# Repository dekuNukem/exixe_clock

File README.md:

# exixe clock: nanosecond-precision GPS-disciplined Nixie tube clock

exixe clock is a GNSS-aided high precision Nixie tube clock.

With GPS fix acquired, displayed time would be within 60 **nanoseconds** of the atomic clocks onboard the satellites.

exixe clock makes use of the [exixe modules](https://github.com/dekuNukem/exixe), and works with both IN-14 and IN-12 tubes. It also comes with a wealth of sensors and interfaces on-board, allowing it to be hacked beyond just a timepiece.

## Video

Here's a short video of exixe clock in action with [exixe14 modules](https://github.com/dekuNukem/exixe) :

https://www.youtube.com/watch?v=r3d2alzgjKc

## Features

### Precision Timing

* 60ns with GPS fix
* less than 1 second per month drift without GPS fix
* Auto time acquisition
* Battery backup
* Customizable timezone

### Simple & modular construction

* Uses [exixe modules](https://github.com/dekuNukem/exixe)
* Works with both IN-12 and IN-14 tubes
* Single 5V supply from USB
* 350mA average consumption

### Versatile interfaces

* USB data transfer / firmware upload
* SD card slot
* Temperature sensor
* Light sensor
* UART extension header
* GNSS debug header
* 2 capacitive touch buttons
* 2 physical buttons
* GNSS fix indicator LED

## User guide

### Setting time

Install a CR1220 coin battery in the holder, connect a GPS antenna and place it under clear sky, time will be automatically set and saved when a GPS fix is obtained. You might have to wait 2 or 3 minutes, but it's usually much faster. Wait until the GPSFIX LED is on for the most accuracy.

### Setting timezone

Unplug the clock, hold down B button then power it back on. The middle two tube will display the UTC offset. Use A and B button to set the offset to your timezone. For negative offsets a dot on the left tube will illuminate.

### 12/24 hour display

Unplug the clock, hold down A button then power it back on. The middle two tube will display either 12 or 24. Use A button to change it.

### Temperature display

Press either A or B button during normal operation to switch the display to temperature in the rightmost two tubes, press it again to switch back.

## Extensions and hacks

There are some extra components that's worth mentioning if you want to further develop upon this project.

* A debug header is situated to the right of the USB port, you can use it for communication or extra GPIOs.

* The GPS header beside the antenna connector breaks out the TX, RX and timepulse of the GPS module, it's mainly for debugging purposes.

* There are 2 capacitive touchpad buttons, they are designed according to the ST reference doc and connected to TSC channels of the STM32, I haven't found a use for them yet though.

* A DFU button is available, hold it down while plugging the clock into a computer puts the STM32 into USB DFU mode, so you can upload firmware through USB without needing a programmer.

* You can use the empty pad of unused components for more GPIOs.

## Parts and tips

* MCU is STM32F072C8T6
* Light sensor is TEMT6000
* Temperature sensor is DS18B20
* GNSS receiver is ublox M8Q (M7Q also works)
* High voltage module is [this one](https://www.ebay.co.uk/itm/DC-5V-12V-to-170V-DC-High-Voltage-NIXIE-Power-Supply-Module-PSU-NIXIE-TUBE-ERA/322511957768?hash=item4b1735ef08:g:ftQAAOSwYTVZmjZb)
* There are two headers for the HV module, use the one that has the correct pinout
* Undefine `USE_EXIXE_14` at the beginning of [my_tasks.c](firmware/Src/my_tasks.c) to use IN-12 tubes.

## Building one yourself

BOM is [here](resources/clock_bom.xlsx)

Making one yourself is fairly straightforward, just order the parts and solder them together. Couple of things to keep in mind though:

There are a couple of optional components that is not used in the current firmware, so you can leave them out if you want, they are highlighted in yellow in the BOM

The temperature sensor DS18B20 has a lot of fakes on the internet, if it's too cheap it's almost certainly fake. Best way is just order through a reputable source like mouser or digikey, it is also optional if you don't want to use this feature.

DO NOT solder the GPS module by hand, it would result in terrible reliability where the GPS module would randomly stop working. Always use paste and reflow.

The PCB works with both exixe12 and exixe14 modules, the only different component is the SMA antenna connector. On clock using exixe14 modules, the right-angle SMA connector is used, while on clock using exixe12 module, a straight SMA connector is used instead. This allows the SMA receptacle point to the back of the clock in both cases.

Front and back plate are need with exixe12 clock to support the PCB inbetween, they are just regular laser cut clear acrylic plates, your local hackerspace should have a laser cutter. The plate files are in the `resources` folder.

You can go without plates with exixe14 clock, although I still recommend getting one for added rigidness. You only need one plate in this case.

To upload firmware to the microcontroller, [see this guide](https://github.com/dekuNukem/exixe/blob/master/making_some.md).

## Rants about conventional Nixie clocks

I was looking through existing Nixie clock projects before starting my own, and I'm rather unconvinced with some trends that many have in common:

* Using through hole components

While there's technically nothing wrong, I feel that in this day and age using PTH looks bulky and unprofessional.

* 12V supply

I want my clock to be powered by a single USB cable, using a 12V powerbrick is both cumbersome and complicates the design.

* Fixed and multiplexed tubes

This is my biggest gripe. With soldered down tubes, it's almost impossible to replace if one breaks, or to repurpose them for other projects. And as Nixie tubes have been out of productions for 30 years, they should be conserved as much as possible.

And as a result of fixed tubes, they are almost always multiplexed. This requires obscure driver chips, complex to route and program, and because only one tube is on at any given time, perceived brightness is 1/6 of what it could be. To compensate, the tubes are often overdriven beyond their max allowed current, reducing their life time. Total mess all around.

* Questionable timekeeping

Let's not forget Nixie clock is first and foremost a clock, and it's useless if it's not good at keeping time. However this aspect almost looks like an afterthought in a lot of the existing Nixie clocks. On many of those time have to be manually entered, and kept with $3 RTC modules from alibaba that drifts 20 seconds a month. I want my clock to be as accurate as possible.

## Things done differently

In the end, I decided to keep the design as modular and as simple as possible. As a result, I designed the exixe driver modules first, then the clock itself later. 

You can read more about the [exixe modules here](https://github.com/dekuNukem/exixe), but in short, they are tiny and inexpensive Nixie tube drivers with hardware PWM on all digits and RGB backlight. Each module controls one tube, and uses SPI for communication.

Now that each tube has its own driver, multiplexing is no longer needed, and routing is down to only 3 SPI lines, and each tube can be replaced and repurposed simply by unplugging the module.

Next up is timing, instead of manually setting time and using built-in RTC, I decided to use GPS-based timekeeping. There are atomic clocks onboard each GPS satellites, and the precise UTC time can be calculated as part of the position fix. This way time can be automatically set and kept within 60ns of GPS time with position fix. Each digit update is triggered by the timepulse signal from the GNSS receiver, synced to the precise transition of each UTC second. And if antenna is disconnected, drift seems to be than 1 second per month from the observation of the one I made myself. A coin battery keeps time even when the clock itself is turned off.

A bunch of extra features was thrown in during the design process as well. I added a temperature sensor so the tubes can optionally display hour:minute:temp instead of hour:minute:second, a blue LED lights up when GPS fix is acquired, 2 capacitive touchpad was added for buttonless controls, a light sensor was added for automatic brightness adjustment, SD card slot was added for data logging, and UART header was added for debugging and expansion.

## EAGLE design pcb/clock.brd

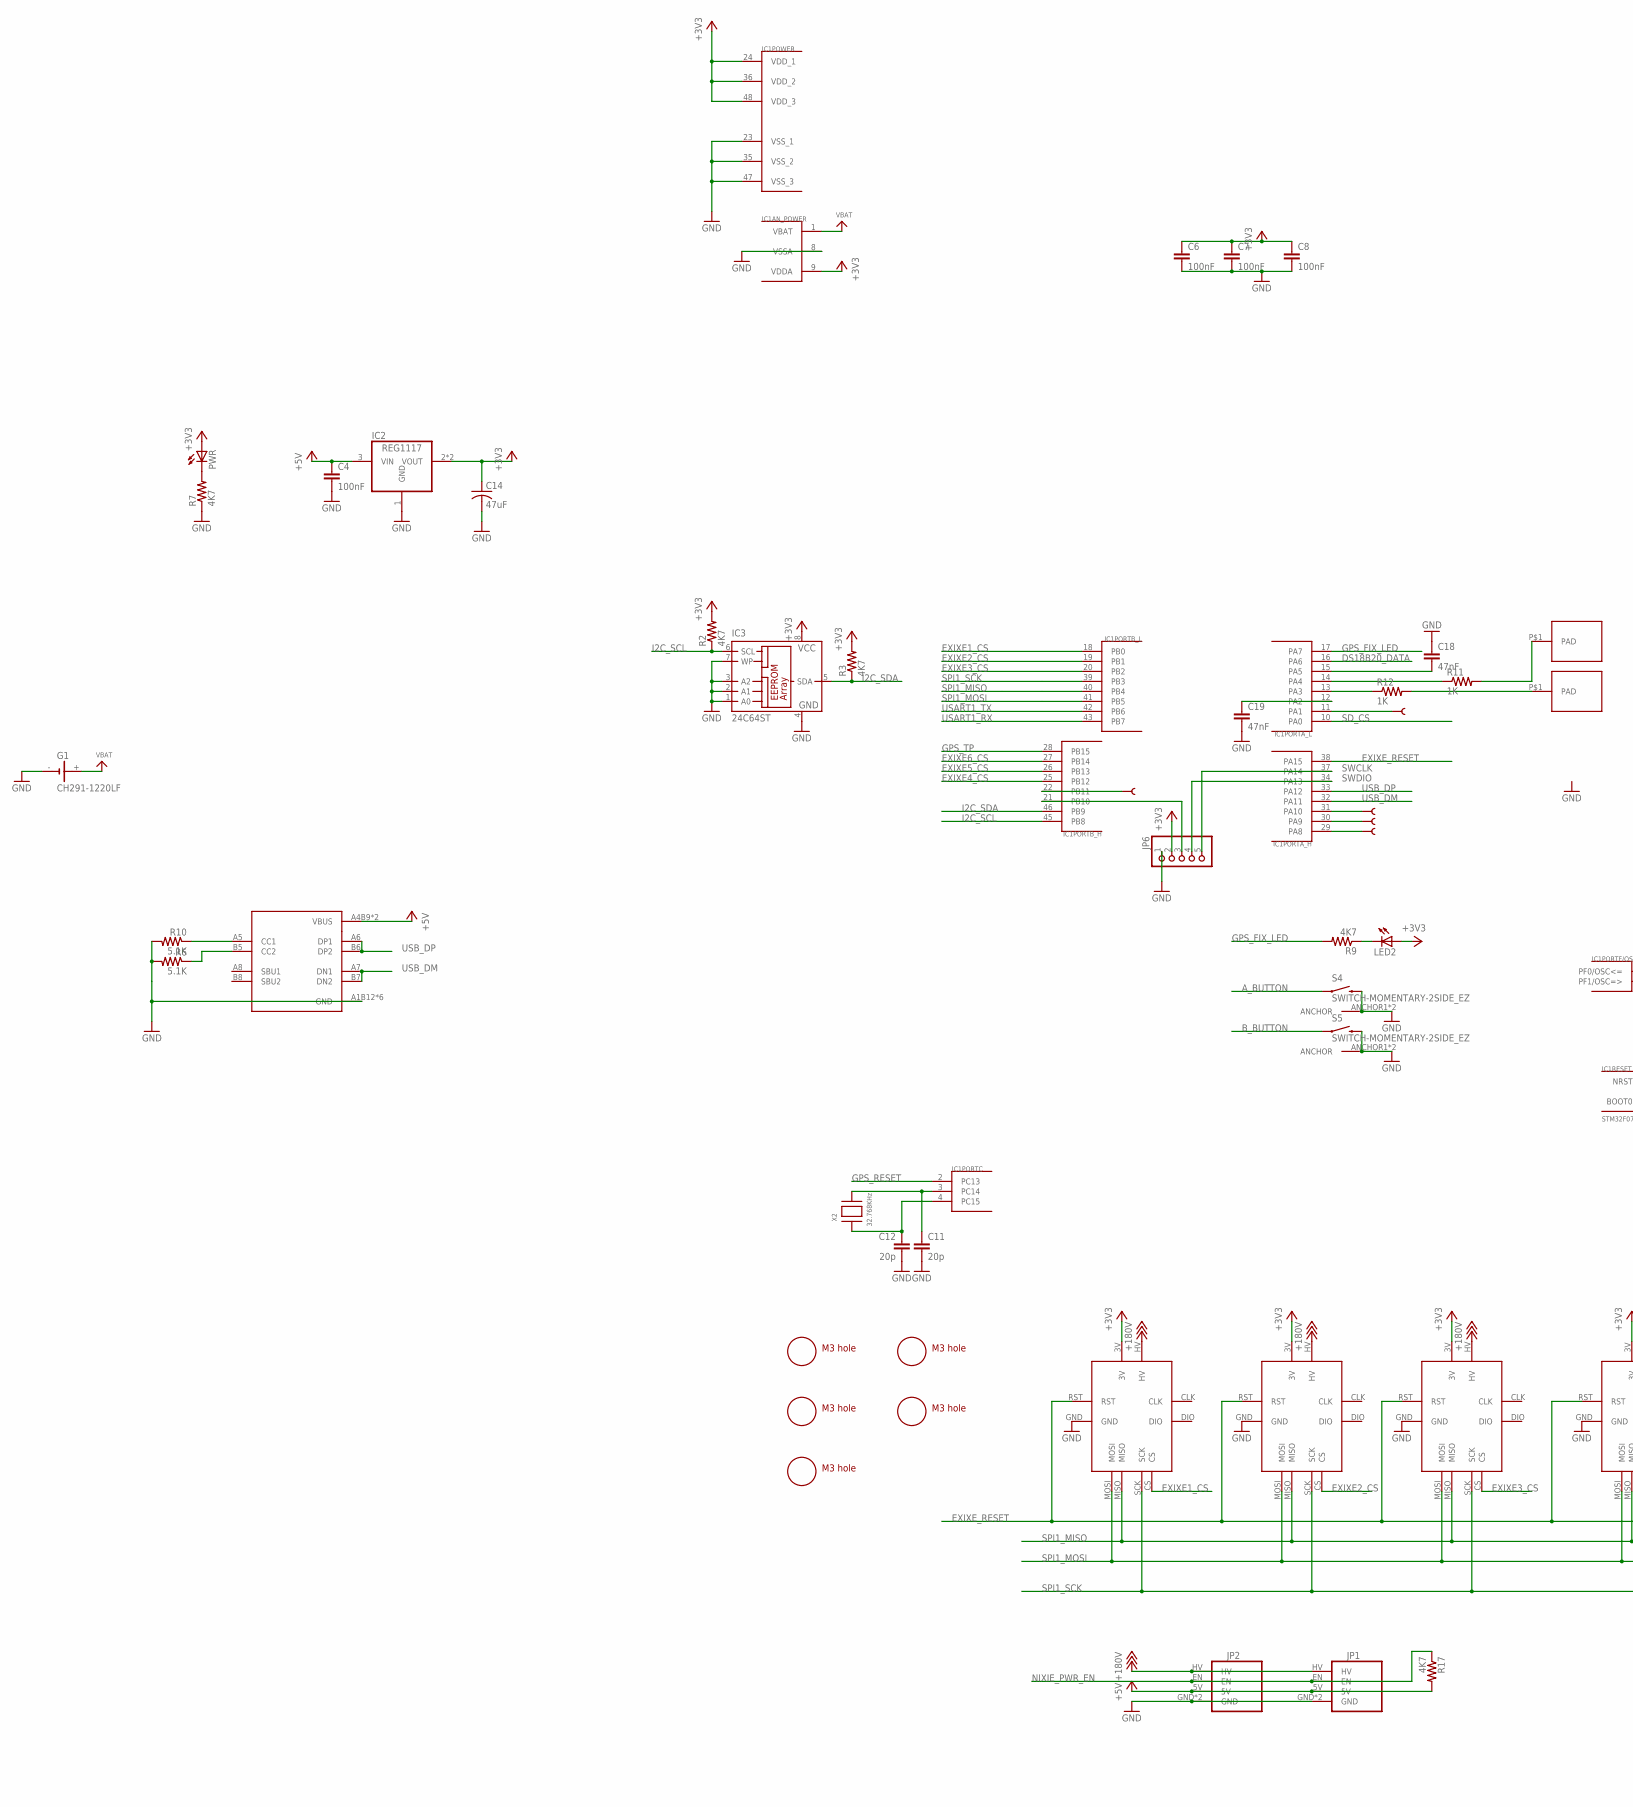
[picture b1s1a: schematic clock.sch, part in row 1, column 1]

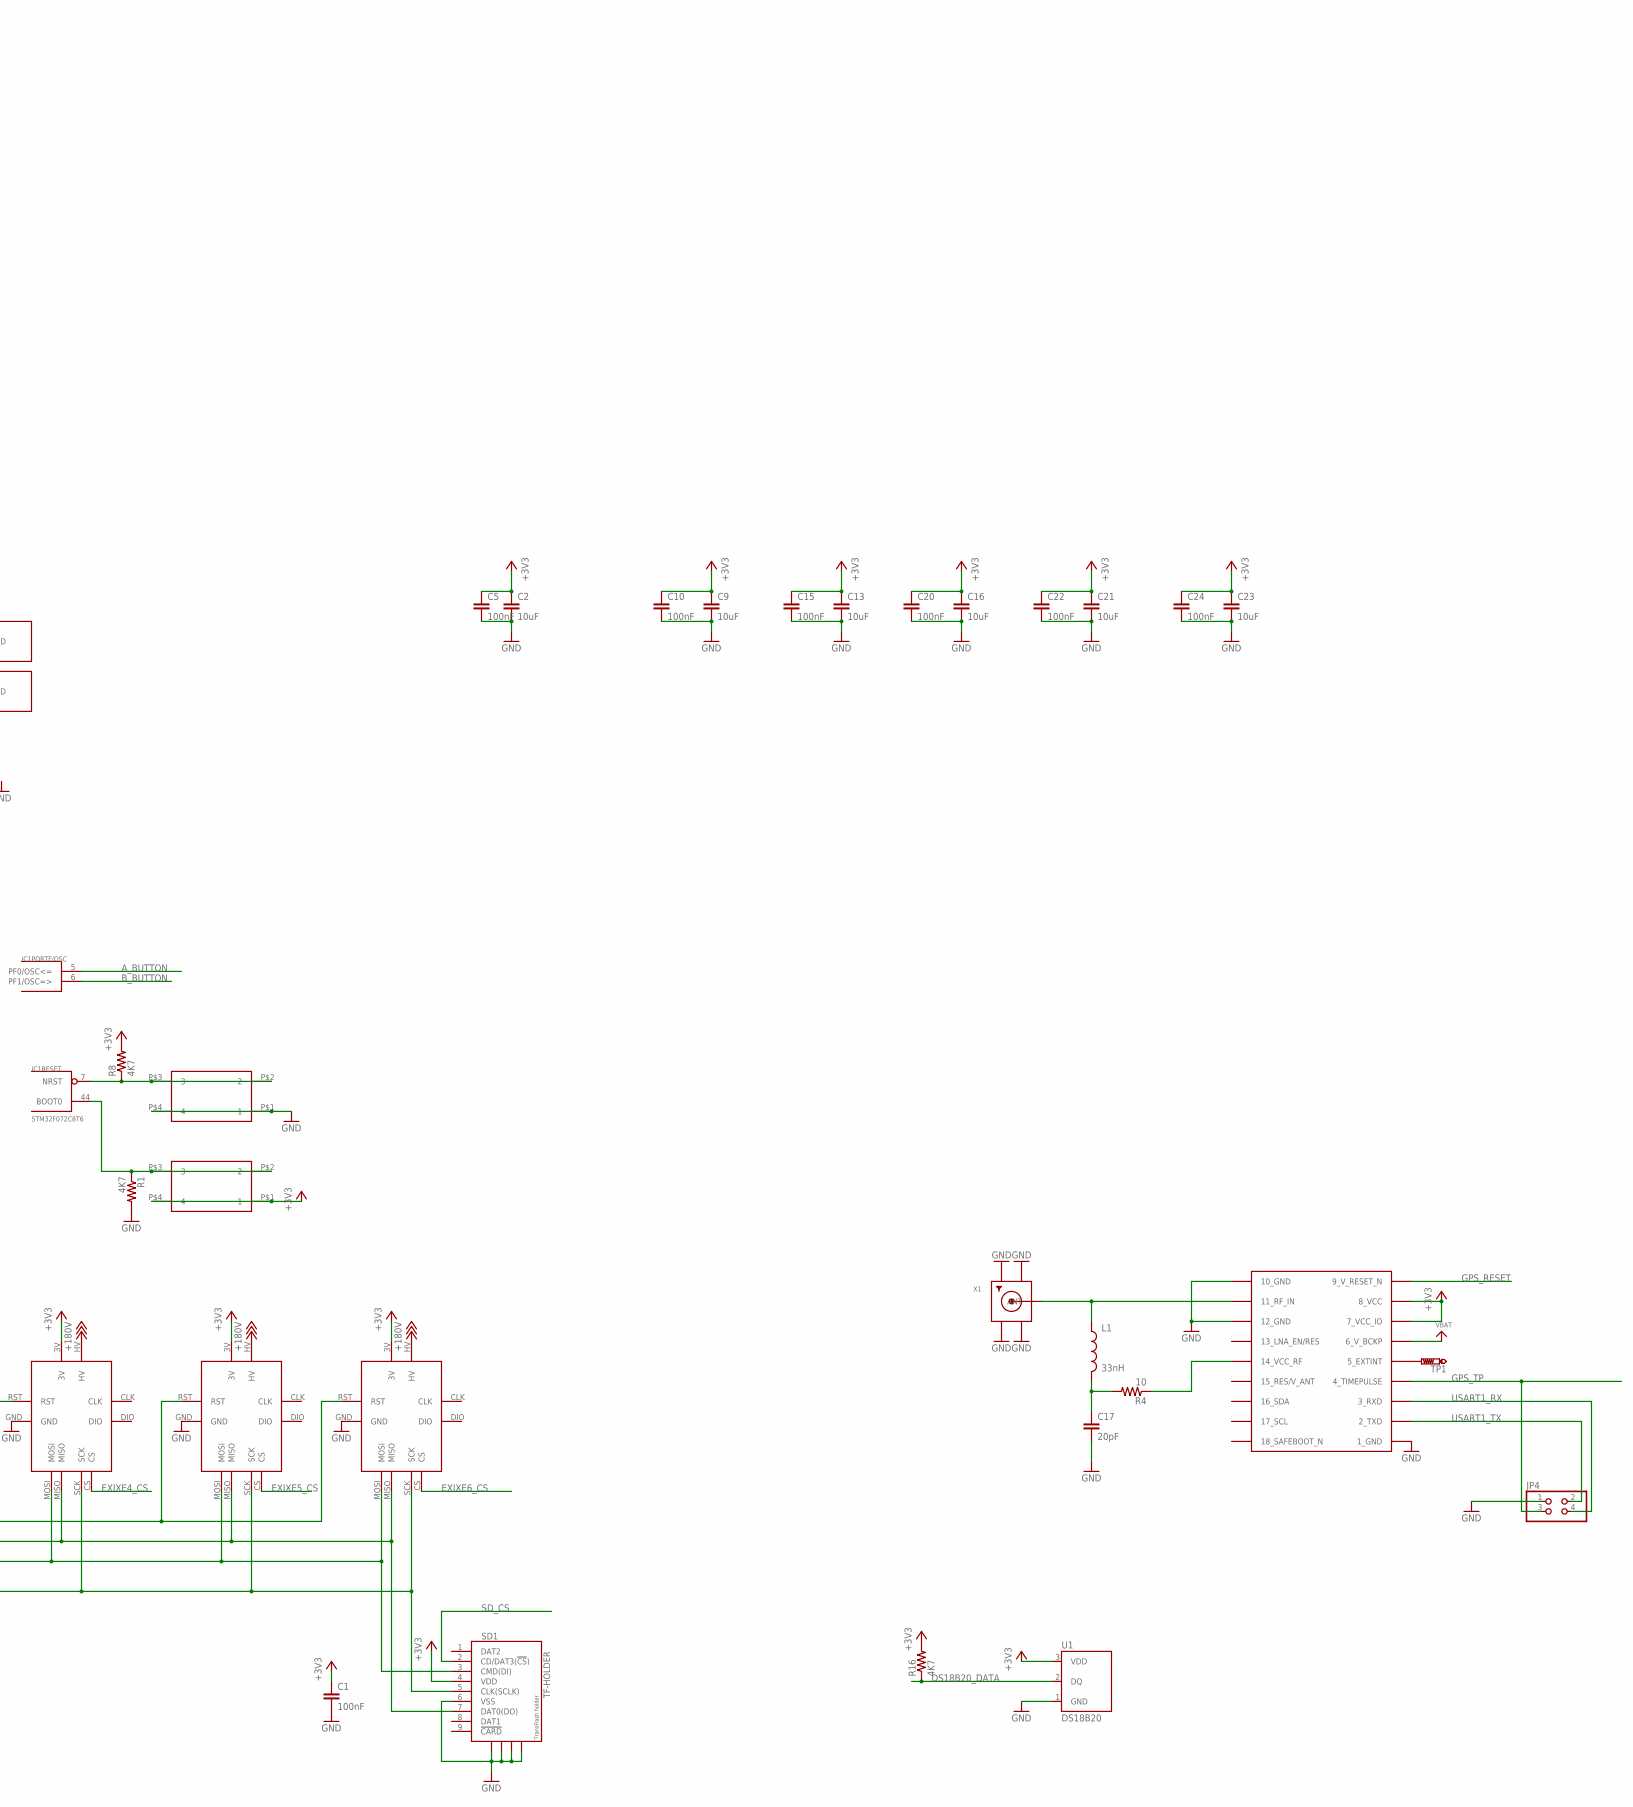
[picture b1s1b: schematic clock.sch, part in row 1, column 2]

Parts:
C1, C4, C5, C6, C7, C8, C10, C15, C20, C22, C24: 100nF; 0805
C2, C9, C13, C16, C21, C23: 10uF; 0805
C11, C12: 20p; 0805
C14: 47uF; C1210
C17: 20pF; 0805
C18, C19: 47nF; 0805
G1: CH291-1220LF
IC1: STM32F072C8T6; TQFP48
IC2: REG1117; SOT223
IC3: 24C64ST; TSSOP8
JP1: EBAY_MODULEEBAY; EBAY_PKG
JP2: EBAY_MODULETAOBAO; TAOBAO_PKG
JP4: PINHD-2X2; 2X02
JP6: PINHD-1X5; 1X05
L1: 33nH; 0805
LED2: LEDCHIP-LED0805; CHIP-LED0805
PWR: LEDCHIP-LED0805; CHIP-LED0805
R1, R2, R3, R7, R8, R9, R16, R17: 4K7; 0805
R4: 10; 0805
R6, R10: 5.1K; 0805
R11, R12: 1K; 0805
S4, S5: SWITCH-MOMENTARY-2SIDE_EZ; TACTILE-PTH-SIDEEZ
SD1: TF-HOLDER; TF-PULL
SW1, SW4: 324_SW324_SWITCH_FOOT_HOLE; 342_SWICH_FOOT_HOLE
TP1: PTR1TP20R; TP20R
TP2, TP3, TP4, TP5, TP6: TEST-POINT3X5; PAD.03X.05
U1: DS18B20; TO-92-AMMO
U2: USBC_16P; USBC_16P_FOOT
U$1, U$2, U$3, U$4, U$5, U$6: EXIXE; EXIXE_PAC
U$7: MAX-M8
U$10, U$11, U$12, U$13, U$20: M3_MOUNTING_HOLE; M3_MOUNTING_HOLE_PACK
U$14, U$15: TOUCHPAD; TOUCHPAD_PAK
X1: SMACONNECTOR; SMA90_DIP
X2: 32.768KHz; XTAL3215

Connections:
+3V3: C1.1, C2.1, C5.1, C6.1, C7.1, C8.1, C9.1, C10.1, C13.1, C14.1, C15.1, C16.1, C20.1, C21.1, C22.1, C23.1, C24.1, IC1.9 (VDDA), IC1.24 (VDD_1), IC1.36 (VDD_2), IC1.48 (VDD_3), IC2.2 (VOUT), IC2.4 (VOUT), IC3.8 (VCC), JP6.2, LED2.A, PWR.A, R2.2, R3.2, R8.2, R16.2, SD1.4 (VDD), SW1.P$1 (1), SW1.P$4 (4), U1.3 (VDD), U$1.3V, U$2.3V, U$3.3V, U$4.3V, U$5.3V, U$6.3V, U$7.7_VCC_IO, U$7.8_VCC
+5V: C4.1, IC2.3 (VIN), JP1.5V, JP2.5V, R17.2, U2.A4B9 (VBUS), U2.B4A9 (VBUS)
+180V: JP1.HV, JP2.HV, U$1.HV, U$2.HV, U$3.HV, U$4.HV, U$5.HV, U$6.HV
A_BUTTON: IC1.5 (PF0/OSC<=), S4.1
B_BUTTON: IC1.6 (PF1/OSC=>), S5.1
DS18B20_DATA: IC1.16 (PA6), R16.1, U1.2 (DQ)
EXIXE1_CS: IC1.18 (PB0), U$1.CS
EXIXE2_CS: IC1.19 (PB1), U$2.CS
EXIXE3_CS: IC1.20 (PB2), U$3.CS
EXIXE4_CS: IC1.25 (PB12), U$4.CS
EXIXE5_CS: IC1.26 (PB13), U$5.CS
EXIXE6_CS: IC1.27 (PB14), U$6.CS
EXIXE_RESET: IC1.38 (PA15), U$1.RST, U$2.RST, U$3.RST, U$4.RST, U$5.RST, U$6.RST
GND: C1.2, C2.2, C4.2, C5.2, C6.2, C7.2, C8.2, C9.2, C10.2, C11.2, C12.2, C13.2, C14.2, C15.2, C16.2, C17.2, C18.1, C19.2, C20.2, C21.2, C22.2, C23.2, C24.2, G1.-, IC1.8 (VSSA), IC1.23 (VSS_1), IC1.35 (VSS_2), IC1.47 (VSS_3), IC2.1 (GND), IC3.1 (A0), IC3.2 (A1), IC3.3 (A2), IC3.4 (GND), IC3.7 (WP), JP1.GND, JP1.GND2 (GND), JP2.GND, JP2.GND2 (GND), JP4.1, JP6.1, R1.2, R6.2, R7.1, R10.2, S4.2, S4.ANCHOR1 (ANCHOR), S4.ANCHOR2 (ANCHOR), S5.2, S5.ANCHOR1 (ANCHOR), S5.ANCHOR2 (ANCHOR), SD1.6 (VSS), SD1.S1, SD1.S2, SD1.S3, SD1.S4, SW4.P$1 (1), SW4.P$4 (4), U1.1 (GND), U2.A1B12 (GND), U2.B11A12 (GND), U2.P$13 (GND), U2.P$14 (GND), U2.P$15 (GND), U2.P$16 (GND), U$1.GND, U$2.GND, U$3.GND, U$4.GND, U$5.GND, U$6.GND, U$7.1_GND, U$7.10_GND, U$7.12_GND, X1.GND1, X1.GND2, X1.GND3, X1.GND4
GPS_FIX_LED: IC1.17 (PA7), R9.2
GPS_RESET: IC1.2 (PC13), U$7.9_RESET_N (9_V_RESET_N)
GPS_TP: IC1.28 (PB15), JP4.3, U$7.4_TIMEPULSE
I2C_SCL: IC1.45 (PB8), IC3.6 (SCL), R2.1
I2C_SDA: IC1.46 (PB9), IC3.5 (SDA), R3.1
unnamed: C11.1, IC1.3 (PC14), X2.P$2
unnamed: C12.1, IC1.4 (PC15), X2.P$1
unnamed: IC1.7 (NRST), R8.1, SW4.P$2 (2), SW4.P$3 (3)
unnamed: L1.1, U$7.11_RF_IN, X1.ANTENNA (ANT)
unnamed: IC1.44 (BOOT0), R1.1, SW1.P$2 (2), SW1.P$3 (3)
unnamed: IC1.31 (PA10), TP2.P$1
unnamed: IC1.30 (PA9), TP3.P$1
unnamed: IC1.14 (PA4), R11.1
unnamed: R11.2, U$15.P$1
unnamed: R12.2, U$14.P$1
unnamed: IC1.13 (PA3), R12.1
unnamed: C17.1, L1.2, R4.2
unnamed: R4.1, U$7.14_VCC_RF
unnamed: C18.2, IC1.15 (PA5)
unnamed: IC1.29 (PA8), TP4.P$1
unnamed: IC1.21 (PB10), JP6.3
unnamed: C19.1, IC1.12 (PA2)
unnamed: LED2.C, R9.1
unnamed: IC1.22 (PB11), TP5.P$1
unnamed: IC1.11 (PA1), TP6.P$1
unnamed: TP1.TP, U$7.5_EXTINT
unnamed: PWR.C, R7.2
unnamed: R6.1, U2.B5 (CC2)
unnamed: R10.1, U2.A5 (CC1)
NIXIE_PWR_EN: JP1.EN, JP2.EN, R17.1
SD_CS: IC1.10 (PA0), SD1.2 (CD/DAT3(!CS!))
SPI1_MISO: IC1.40 (PB4), SD1.7 (DAT0(DO)), U$1.MISO, U$2.MISO, U$3.MISO, U$4.MISO, U$5.MISO, U$6.MISO
SPI1_MOSI: IC1.41 (PB5), SD1.3 (CMD(DI)), U$1.MOSI, U$2.MOSI, U$3.MOSI, U$4.MOSI, U$5.MOSI, U$6.MOSI
SPI1_SCK: IC1.39 (PB3), SD1.5 (CLK(SCLK)), U$1.SCK, U$2.SCK, U$3.SCK, U$4.SCK, U$5.SCK, U$6.SCK
SWCLK: IC1.37 (PA14), JP6.5
SWDIO: IC1.34 (PA13), JP6.4
USART1_RX: IC1.43 (PB7), JP4.4, U$7.3_RXD
USART1_TX: IC1.42 (PB6), JP4.2, U$7.2_TXD
USB_DM: IC1.32 (PA11), U2.A7 (DN1), U2.B7 (DN2)
USB_DP: IC1.33 (PA12), U2.A6 (DP1), U2.B6 (DP2)
VBAT: G1.+, IC1.1 (VBAT), U$7.6_V_BCKP

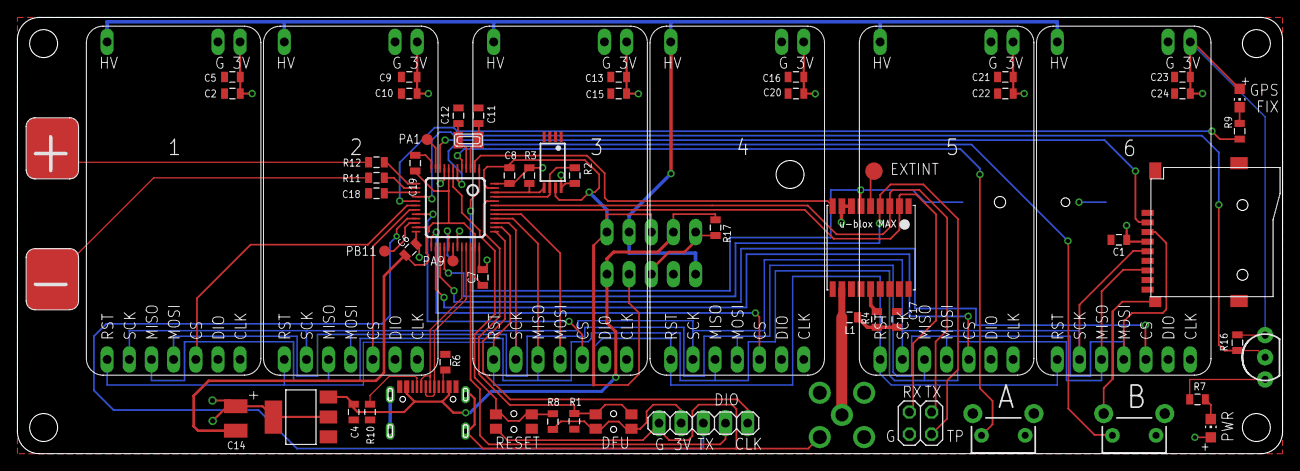
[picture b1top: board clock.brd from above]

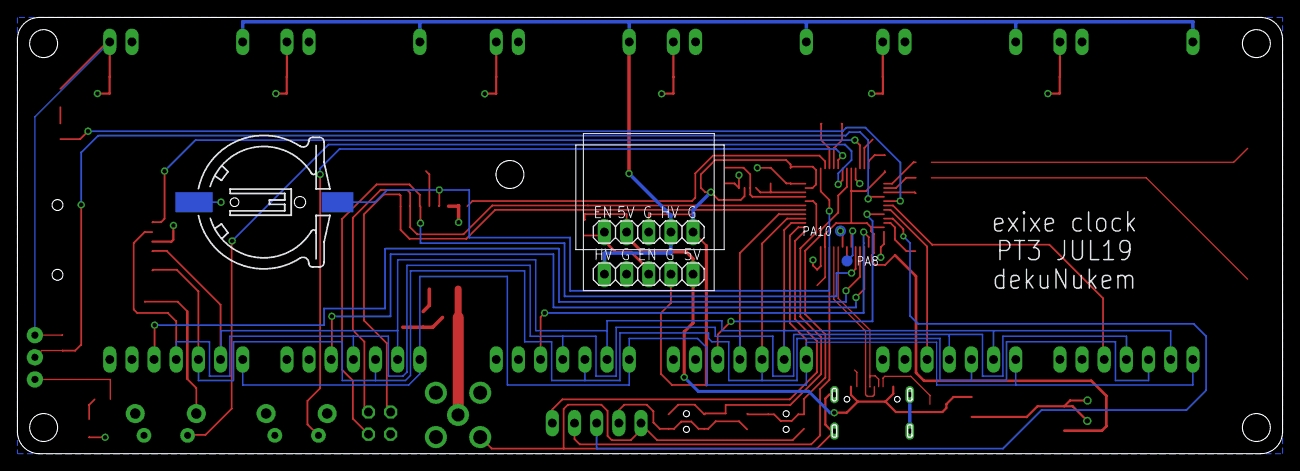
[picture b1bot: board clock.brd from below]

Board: 2 copper layers, 144.8 x 49.8 mm, 76 parts (5 on the bottom side), 55 nets.

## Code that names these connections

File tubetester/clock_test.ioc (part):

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Mcu.Name=STM32F072C(8-B)Tx
Mcu.Package=LQFP48
Mcu.UserName=STM32F072C8Tx
PA0.GPIOParameters=PinState,GPIO_Label,GPIO_ModeDefaultOutputPP
PA0.GPIO_Label=SD_CS
PA0.GPIO_ModeDefaultOutputPP=GPIO_MODE_OUTPUT_PP
PA0.PinState=GPIO_PIN_SET
PA0.Signal=GPIO_Output
PA1.Mode=IN1
PA1.Signal=ADC_IN1
PA11.Mode=Device
PA11.Signal=USB_DM
PA12.Mode=Device
PA12.Signal=USB_DP
PA13.Mode=Serial_Wire
PA13.Signal=SYS_SWDIO
PA14.Mode=Serial_Wire
PA14.Signal=SYS_SWCLK
PA15.GPIOParameters=PinState,GPIO_Label,GPIO_ModeDefaultOutputPP
PA15.GPIO_Label=EXIXE_RESET
PA15.GPIO_ModeDefaultOutputPP=GPIO_MODE_OUTPUT_OD
PA15.PinState=GPIO_PIN_SET
PA15.Signal=GPIO_Output
PA6.GPIOParameters=PinState,GPIO_Label,GPIO_ModeDefaultOutputPP
PA6.GPIO_Label=OWIRE_DATA
PA6.GPIO_ModeDefaultOutputPP=GPIO_MODE_OUTPUT_OD
PA6.PinState=GPIO_PIN_SET
PA6.Signal=GPIO_Output
PA7.GPIOParameters=PinState,GPIO_Label
PA7.GPIO_Label=USER_LED
PA7.PinState=GPIO_PIN_SET
PA7.Signal=GPIO_Output
PB0.GPIOParameters=PinState,GPIO_Label
PB0.GPIO_Label=EXIXE1_CS
PB0.PinState=GPIO_PIN_SET
PB0.Signal=GPIO_Output
PB1.GPIOParameters=PinState,GPIO_Label
PB1.GPIO_Label=EXIXE2_CS
PB1.PinState=GPIO_PIN_SET
PB1.Signal=GPIO_Output
PB10.Mode=Asynchronous
PB10.Signal=USART3_TX
PB11.Mode=Asynchronous
PB11.Signal=USART3_RX
PB12.GPIOParameters=PinState,GPIO_Label
PB12.GPIO_Label=EXIXE4_CS
PB12.PinState=GPIO_PIN_SET
PB12.Signal=GPIO_Output
PB13.GPIOParameters=PinState,GPIO_Label
PB13.GPIO_Label=EXIXE5_CS
PB13.PinState=GPIO_PIN_SET
PB13.Signal=GPIO_Output
PB14.GPIOParameters=PinState,GPIO_Label
PB14.GPIO_Label=EXIXE6_CS
PB14.PinState=GPIO_PIN_SET
PB14.Signal=GPIO_Output
PB15.GPIOParameters=GPIO_Label,GPIO_ModeDefaultEXTI
PB15.GPIO_Label=GPS_TP
PB15.GPIO_ModeDefaultEXTI=GPIO_MODE_IT_RISING
PB15.Signal=GPXTI15
PB2.GPIOParameters=PinState,GPIO_Label
PB2.GPIO_Label=EXIXE3_CS
PB2.PinState=GPIO_PIN_SET
PB2.Signal=GPIO_Output
PB3.Mode=Full_Duplex_Master
PB3.Signal=SPI1_SCK
PB4.Mode=Full_Duplex_Master
PB4.Signal=SPI1_MISO
PB5.Mode=Full_Duplex_Master
PB5.Signal=SPI1_MOSI
PB6.Mode=Asynchronous
PB6.Signal=USART1_TX
PB7.Mode=Asynchronous
PB7.Signal=USART1_RX
PB8.Mode=I2C
PB8.Signal=I2C1_SCL
PB9.Mode=I2C
PB9.Signal=I2C1_SDA
PC13.GPIOParameters=PinState,GPIO_Label
PC13.GPIO_Label=GPS_RESET
PC13.PinState=GPIO_PIN_SET
PC13.Signal=GPIO_Output
PF0-OSC_IN.GPIOParameters=GPIO_PuPd,GPIO_Label
PF0-OSC_IN.GPIO_Label=UP_BUTTON
PF0-OSC_IN.GPIO_PuPd=GPIO_PULLUP
PF0-OSC_IN.Signal=GPIO_Input
PF1-OSC_OUT.GPIOParameters=GPIO_PuPd,GPIO_Label
PF1-OSC_OUT.GPIO_Label=DOWN_BUTTON
PF1-OSC_OUT.GPIO_PuPd=GPIO_PULLUP
PF1-OSC_OUT.Signal=GPIO_Input
RCC.SYSCLKFreq_VALUE=48000000
RCC.SYSCLKSource=RCC_SYSCLKSOURCE_HSI48
board=clock_test

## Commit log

2017-10-25 added switch for IN-12 and IN-14 tubes
2017-10-25 writing readme
2017-10-26 more readme
2017-11-01 disabled iwdg
2017-11-03 reenabled watchdog, reduced startup delay
2017-11-03 reduced RTC clibration time
2017-11-21 forgot what I did
2017-11-22 added bom
2017-11-22 updated bom
2017-11-30 cleanup
2017-11-30 adjusted readme structure
2017-11-30 rephrase readme
2017-11-30 added video in readme
2017-11-30 added license
2017-12-04 added more photos
2017-12-14 added tube tester firmware
2017-12-14 clean up tube tester firmware
2017-12-29 adjusted plate length
2018-06-10 added HEX files
2019-01-14 added a simpler firmware version. Removed USB and temperature function, use the physical button to change timezone whenever, reduced code size
2019-06-30 updated to USBC connector
2019-07-04 moved header
2019-07-04 clean up
2019-07-22 added v1 pcbs back, added some readmes, cleanup
2019-07-22 rearranged README
2019-07-22 updated README to reflect v2 boards
2019-07-23 fixed a silkscreen error on PCB
2019-10-25 added gerber files
2020-12-21 updated commit scripts
2025-06-30 revisit
2025-06-30 compiles before sd]
2025-06-30 ff compiles
2025-06-30 TP interrupt show rmc time, led lights up when rmc has time
2025-06-30 before removing rtc
2025-06-30 removed rtc
2025-06-30 mountsd working
2025-06-30 printjson, before changing interrupt priority
2025-06-30 UART interrupt priority
2025-06-30 correct second
2025-06-30 logging working, uart flaky
2025-06-30 done
2025-07-01 done for now, needs to sort out UART dropping
2025-08-02 log temp as float

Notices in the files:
parts and their libraries:
SparkFun-Sensors: Licensing: Creative Commons ShareAlike 4.0 International - https://creativecommons.org/licenses/by-sa/4.0
